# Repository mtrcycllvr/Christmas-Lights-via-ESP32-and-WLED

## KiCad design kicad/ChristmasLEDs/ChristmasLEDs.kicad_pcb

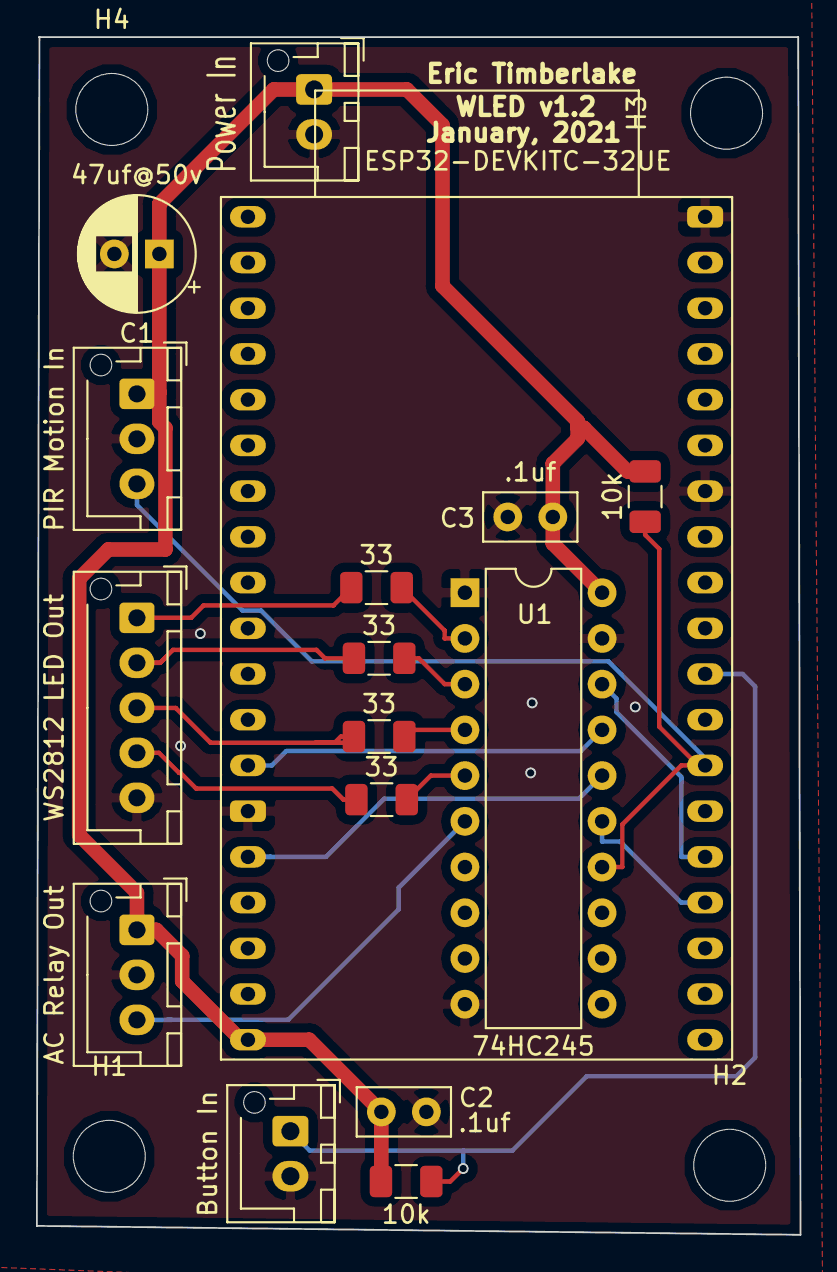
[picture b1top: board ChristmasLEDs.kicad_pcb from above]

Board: 2 copper layers, 42.4 x 66.6 mm, 20 parts (0 on the bottom side), 17 nets.

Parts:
C1: 47uf@50v; CP_Radial_D6.3mm_P2.50mm
C2, C3: .1uf; C_Disc_D5.0mm_W2.5mm_P2.50mm
ESP32-DEVKITC-32UE: ESP32-DevKitC
H1, H2, H3, H4: MountingHole; MountingHole_4mm
J1: Power In; JST_XH_B02B-XH-AM_1x02_P2.50mm_Vertical
J2: PIR Motion In; JST_XH_B03B-XH-AM_1x03_P2.50mm_Vertical
J3: AC Relay Out; JST_XH_B03B-XH-AM_1x03_P2.50mm_Vertical
J4: WS2812 LED Out; JST_XH_B05B-XH-AM_1x05_P2.50mm_Vertical
J6: Button In; JST_XH_B02B-XH-AM_1x02_P2.50mm_Vertical
R1, R2, R3, R4: 33; R_1206_3216Metric
R5, R6: 10k; R_1206_3216Metric
U1: 74HC245; DIP-20_W7.62mm

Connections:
+5V: C1.1, C2.1, C3.1, ESP32-DEVKITC-32UE.19, J1.1, J2.1, J3.1, R5.1, R6.1, U1.20
/GPIO2: ESP32-DEVKITC-32UE.24, U1.18
/GPIO2b: R1.1, U1.2
/GPIO4: ESP32-DEVKITC-32UE.26, J2.3, R5.2, U1.14
/GPIO4b: J3.3, U1.6
/GPIO12: ESP32-DEVKITC-32UE.13, U1.17
/GPIO12b: R2.1, U1.3
/GPIO13: ESP32-DEVKITC-32UE.15, U1.16
/GPIO13b: R3.1, U1.4
/GPIO15: ESP32-DEVKITC-32UE.23, U1.15
/GPIO15b: R4.1, U1.5
/GPIO17: ESP32-DEVKITC-32UE.28, J6.1, R6.2
GND: C1.2, C2.2, C3.2, ESP32-DEVKITC-32UE.14, ESP32-DEVKITC-32UE.32, ESP32-DEVKITC-32UE.38, J1.2, J2.2, J3.2, J4.5, J6.2, U1.1, U1.10, U1.19
unnamed: J4.1, R1.2
unnamed: J4.2, R2.2
unnamed: J4.3, R3.2
unnamed: J4.4, R4.2

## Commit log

2022-01-25 Update board error!!
